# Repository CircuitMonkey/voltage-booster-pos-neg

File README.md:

# voltage-booster-pos-neg
Low voltage to +/-9V voltage booster circuit using MIC2145.

## About this Circuit
Experimental PCB that boosts nominal 3.7V to 9VDC while also adding
a -9VDC rail.  I needed both +9 and -9 for an analog sythesizer experiment
but my power supply design got a little complicated and expensive using
Pololu boost modules.  Once I built my synth circuit, I was able to characterize
my power needs (about 200mA at 9V and much less at -9V).

Based on this application note from Texas Instruments:
https://www.ti.com/lit/an/slvaej3/slvaej3.pdf

Will it work?

## Images

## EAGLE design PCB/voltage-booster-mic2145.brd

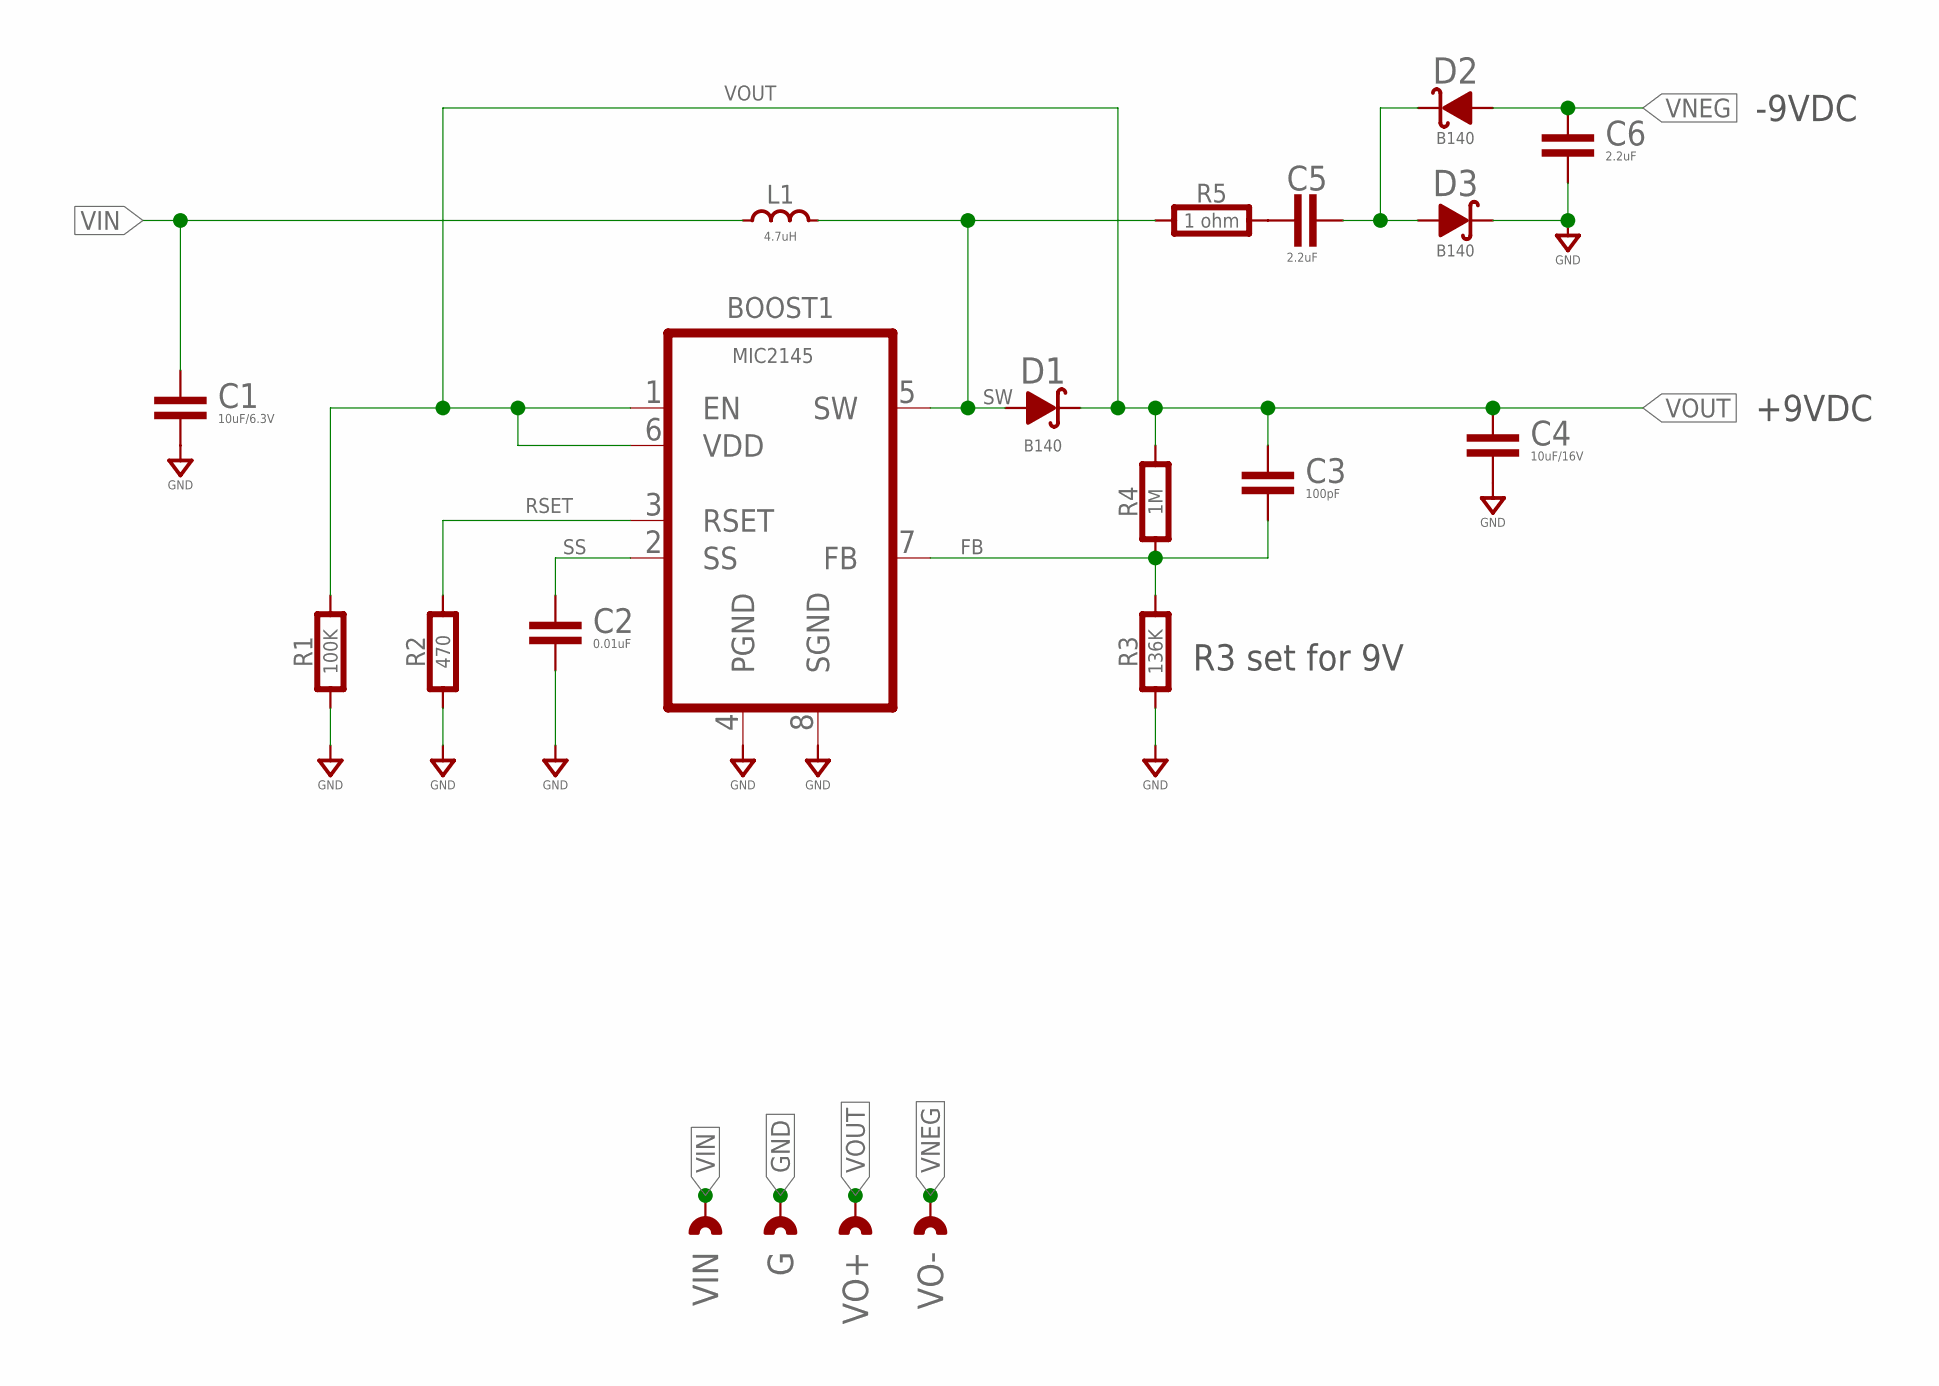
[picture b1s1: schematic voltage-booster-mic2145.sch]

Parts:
BOOST1: MIC2145; MSOP8-0.65
C1: 10uF/6.3V; 0603-CAP
C2: 0.01uF; 0603-CAP
C3: 100pF; 0603-CAP
C4: 10uF/16V; 0603-CAP
C5, C6: 2.2uF; 0603-CAP
D1, D2, D3: B140; SMA
G: CAST-01X12.54MM; CAST01-2.54MM
L1: 4.7uH; IND-SRN5040
R1: 100K; 0603-RES
R2: 470; 0603-RES
R3: 136K; 0603-RES
R4: 1M; 0603-RES
R5: 1 ohm; 0603-RES
VIN: CAST-01X12.54MM; CAST01-2.54MM
VO+: CAST-01X12.54MM; CAST01-2.54MM
VO-: CAST-01X12.54MM; CAST01-2.54MM

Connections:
FB: BOOST1.7 (FB), C3.2, R3.2, R4.1
GND: BOOST1.4 (PGND), BOOST1.8 (SGND), C1.2, C2.2, C4.2, C6.2, D3.K, G.1, R1.1, R2.1, R3.1
unnamed: C5.1, R5.2
unnamed: C5.2, D2.K, D3.A
RSET: BOOST1.3 (RSET), R2.2
SS: BOOST1.2 (SS), C2.1
SW: BOOST1.5 (SW), D1.A, L1.1, R5.1
VIN: C1.1, L1.2, VIN.1
VNEG: C6.1, D2.A, VO-.1
VOUT: BOOST1.1 (EN), BOOST1.6 (VDD), C3.1, C4.1, D1.K, R1.2, R4.2, VO+.1

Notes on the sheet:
R3 set for 9V
-9VDC
+9VDC

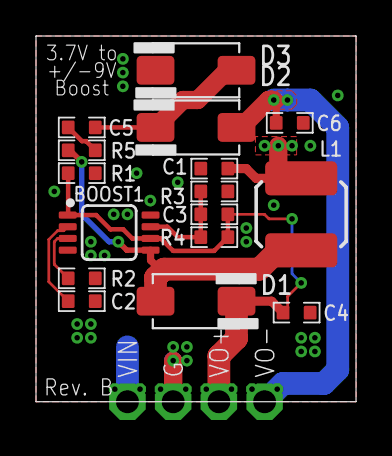
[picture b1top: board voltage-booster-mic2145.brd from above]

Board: 2 copper layers, 17.8 x 20.3 mm, 20 parts (0 on the bottom side), 10 nets.

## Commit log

2022-06-07 Rev. A
2022-06-07 Add PCB images
2022-06-20 Ad/update component values.
2022-06-20 Datasheet, create BOM, document schematic
2022-06-20 Update gitignore
2022-06-20 Fix error where neg-volt section on wrong signal.
    Bumped rev to B
2022-08-06 Added schematic notes.
